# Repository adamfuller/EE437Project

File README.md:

# EE437Project
Autonomous robot car with a smartphone interface

# TODO
- [x] Code for servo
- [x] Add screw holes to board (Adam - 10/16)
- [x] Incorporate Arduino IC into board (Adam - 10/15)
- [x] Add signal lights (forward, backward, turn)
- [x] Design signal lights board
- [ ] Finalize Controller Board Design
- [ ] Submit board design and parts list
- [ ] Assemble board
- [ ] Test board

# Parts List
## Controller Board
- [ ] 1x ATMega328 IC
- [ ] 1x 16 MHz Crystal
- [ ] 1x 28pin socket
- [ ] 1x 4 pin header - male
- [ ] 1x 3 pin header - male
- [ ] 1x 6 pin header - female 90°
- [ ] 2x 2 slot terminal blocks
- [ ] 2x 2x6 header - male
- [ ] 1x power jack
- [ ] 8x 1n4004 diodes
- [ ] 2x 220uF capacitor
- [ ] 2x 20pF capacitor
- [ ] 2x 1k resistor
- [ ] 1x 2k resistor
- [ ] 1x 5mm LED
- [ ] Wire

## Signal Lights Board
- [ ] 12x 5mm LED
- [ ] 4x 300 resistor
- [ ] 4x 4 pin header - male

# Stand-alone Custom Board

# Stand-alone Custom Board Schematic

# Stand-alone Custom Board Manufacturing Preview

## Top

## Bottom

# Custom Shield Board

# Custom Shield Schematic

# Custom Shield Manufacturing Preview

## Top

## Bottom

# Reduced Custom Board

# Reduced Custom Board Schematic

# Reduced Custom Board Manufacturing Preview

## Top

## Bottom

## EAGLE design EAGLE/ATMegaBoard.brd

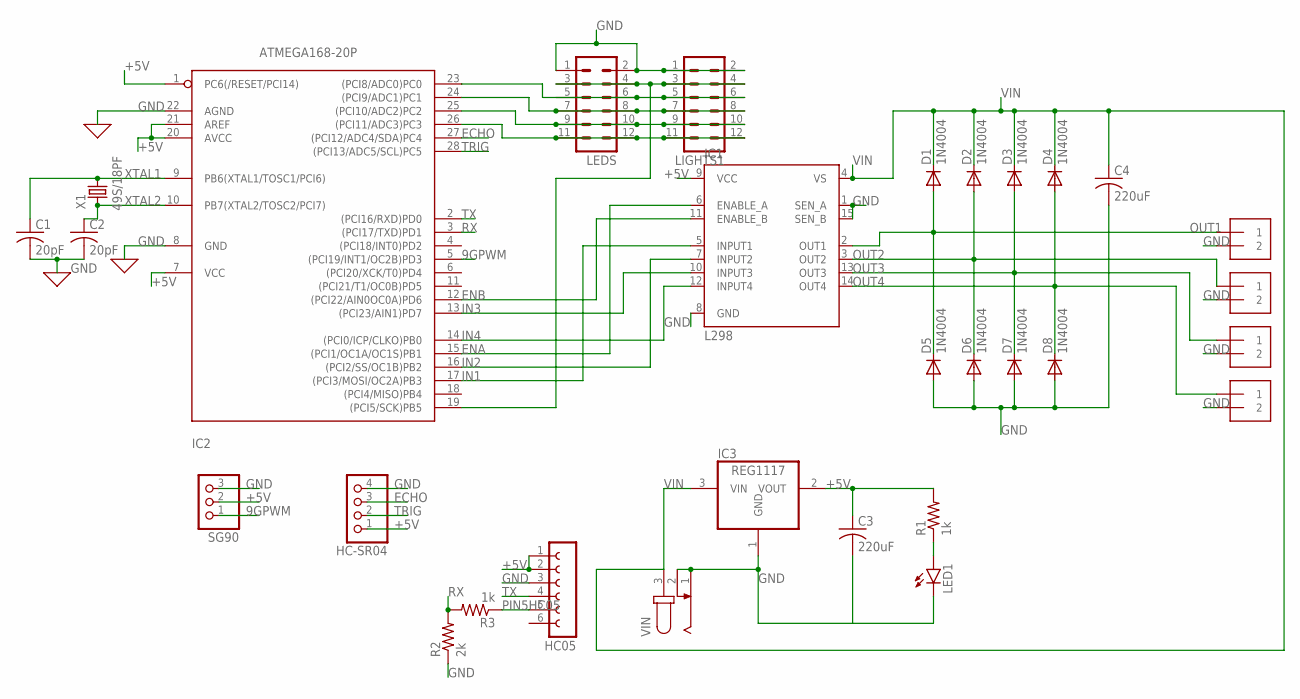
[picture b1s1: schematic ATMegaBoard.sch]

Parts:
C1, C2: 20pF; C050-024X044
C3, C4: 220uF; C050-024X044
D1, D2, D3, D4, D5, D6, D7, D8: 1N4004; DO41-10
HC05: FE06W
HC-SR04: PINHD-1X4; 1X04
IC1: L298; MULTIWATT-15
IC2: ATMEGA168-20P; DIL28-3
IC3: REG1117; SOT223
LED1: LED5MM
LEDS: MA06-2
LIGHTS1: MA06-2
OUT1, OUT2, OUT3, OUT4: 1X2-3.5MM
R1, R3: 1k; 0207/10
R2: 2k; 0207/10
SG90: PINHD-1X3; 1X03
VIN: JACK-PLUG1; SPC4078
X1: 49S/18PF; XTAL_HC49

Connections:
9GPWM: IC2.5 ((PCI19/INT1/OC2B)PD3), SG90.1
+5V: C3.1, HC05.1, HC05.2, HC-SR04.1, IC1.9 (VCC), IC2.1 (PC6(/RESET/PCI14)), IC2.7 (VCC), IC2.20 (AVCC), IC2.21 (AREF), IC3.2 (VOUT), R1.2, SG90.2
ECHO: HC-SR04.3, IC2.27 ((PCI12/ADC4/SDA)PC4)
ENA: IC1.6 (ENABLE_A), IC2.15 ((PCI1/OC1A/OC1S)PB1)
ENB: IC1.11 (ENABLE_B), IC2.12 ((PCI22/AIN0OC0A)PD6)
GND: C1.2, C2.2, C3.2, C4.2, D5.A, D6.A, D7.A, D8.A, HC05.3, HC-SR04.4, IC1.1 (SEN_A), IC1.8 (GND), IC1.15 (SEN_B), IC2.8 (GND), IC2.22 (AGND), IC3.1 (GND), LED1.K (C), LEDS.1, LEDS.2, LIGHTS1.1, LIGHTS1.2, OUT1.2, OUT2.2, OUT3.2, OUT4.2, R2.1, SG90.3, VIN.1, VIN.2
IN1: IC1.5 (INPUT1), IC2.17 ((PCI3/MOSI/OC2A)PB3)
IN2: IC1.7 (INPUT2), IC2.16 ((PCI2/SS/OC1B)PB2)
IN3: IC1.10 (INPUT3), IC2.13 ((PCI23/AIN1)PD7)
IN4: IC1.12 (INPUT4), IC2.14 ((PCI0/ICP/CLKO)PB0)
unnamed: IC2.23 ((PCI8/ADC0)PC0), LEDS.5, LEDS.6, LIGHTS1.5, LIGHTS1.6
unnamed: LED1.A, R1.1
unnamed: IC2.24 ((PCI9/ADC1)PC1), LEDS.7, LEDS.8, LIGHTS1.7, LIGHTS1.8
unnamed: IC2.25 ((PCI10/ADC2)PC2), LEDS.9, LEDS.10, LIGHTS1.9, LIGHTS1.10
unnamed: IC2.19 ((PCI5/SCK)PB5), LEDS.3, LEDS.4, LIGHTS1.3, LIGHTS1.4
unnamed: IC2.26 ((PCI11/ADC3)PC3), LEDS.11, LEDS.12, LIGHTS1.11, LIGHTS1.12
OUT1: D1.A, D5.C, IC1.2 (OUT1), OUT1.1
OUT2: D2.A, D6.C, IC1.3 (OUT2), OUT2.1
OUT3: D3.A, D7.C, IC1.13 (OUT3), OUT3.1
OUT4: D4.A, D8.C, IC1.14 (OUT4), OUT4.1
PIN5HC05: HC05.5, R3.1
RX: IC2.3 ((PCI17/TXD)PD1), R2.2, R3.2
TRIG: HC-SR04.2, IC2.28 ((PCI13/ADC5/SCL)PC5)
TX: HC05.4, IC2.2 ((PCI16/RXD)PD0)
VIN: C4.1, D1.C, D2.C, D3.C, D4.C, IC1.4 (VS), IC3.3 (VIN), VIN.3
XTAL1: C1.1, IC2.9 (PB6(XTAL1/TOSC1/PCI6)), X1.2
XTAL2: C2.1, IC2.10 (PB7(XTAL2/TOSC2/PCI7)), X1.1

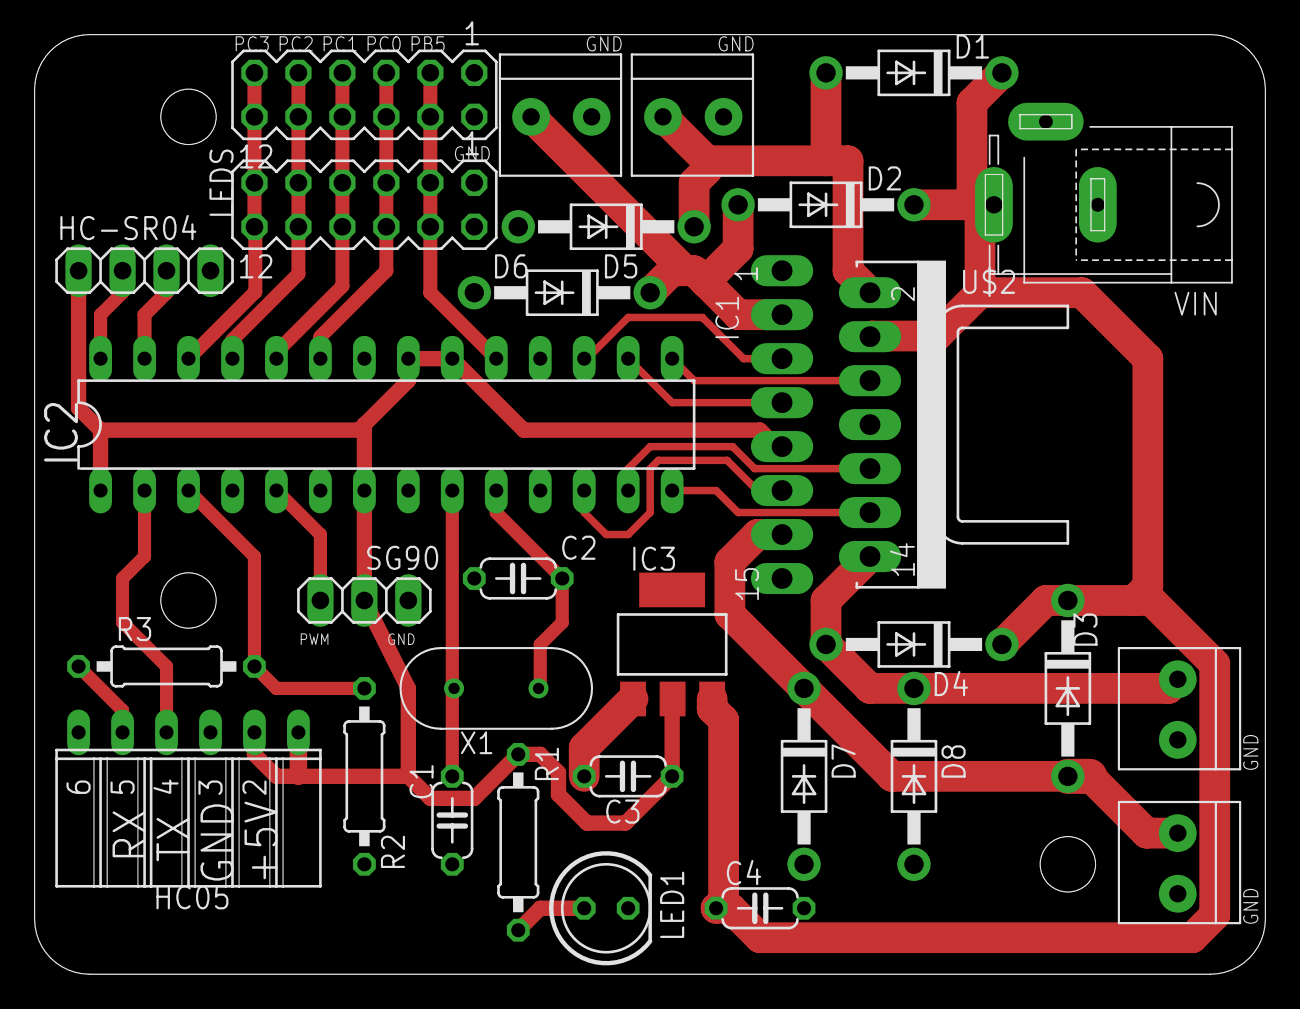
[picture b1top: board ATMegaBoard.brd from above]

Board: 2 copper layers, 71.1 x 54.3 mm, 31 parts (0 on the bottom side), 27 nets.

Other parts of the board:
U$2: D03S

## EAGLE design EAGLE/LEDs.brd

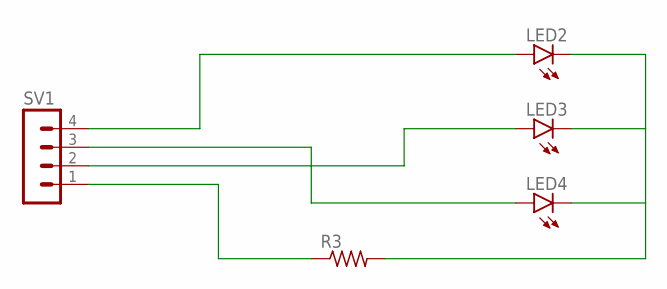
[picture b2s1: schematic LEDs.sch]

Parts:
LED2, LED3, LED4: LED5MM
R3: R-US_0204/7; 0204/7
SV1: MA04-1

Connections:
unnamed: LED2.A, SV1.4
unnamed: LED4.A, SV1.3
unnamed: LED3.A, SV1.2
unnamed: LED2.K (C), LED3.K (C), LED4.K (C), R3.2
unnamed: R3.1, SV1.1

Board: 2 copper layers, 5 parts (0 on the bottom side), 5 nets, no tracks yet.

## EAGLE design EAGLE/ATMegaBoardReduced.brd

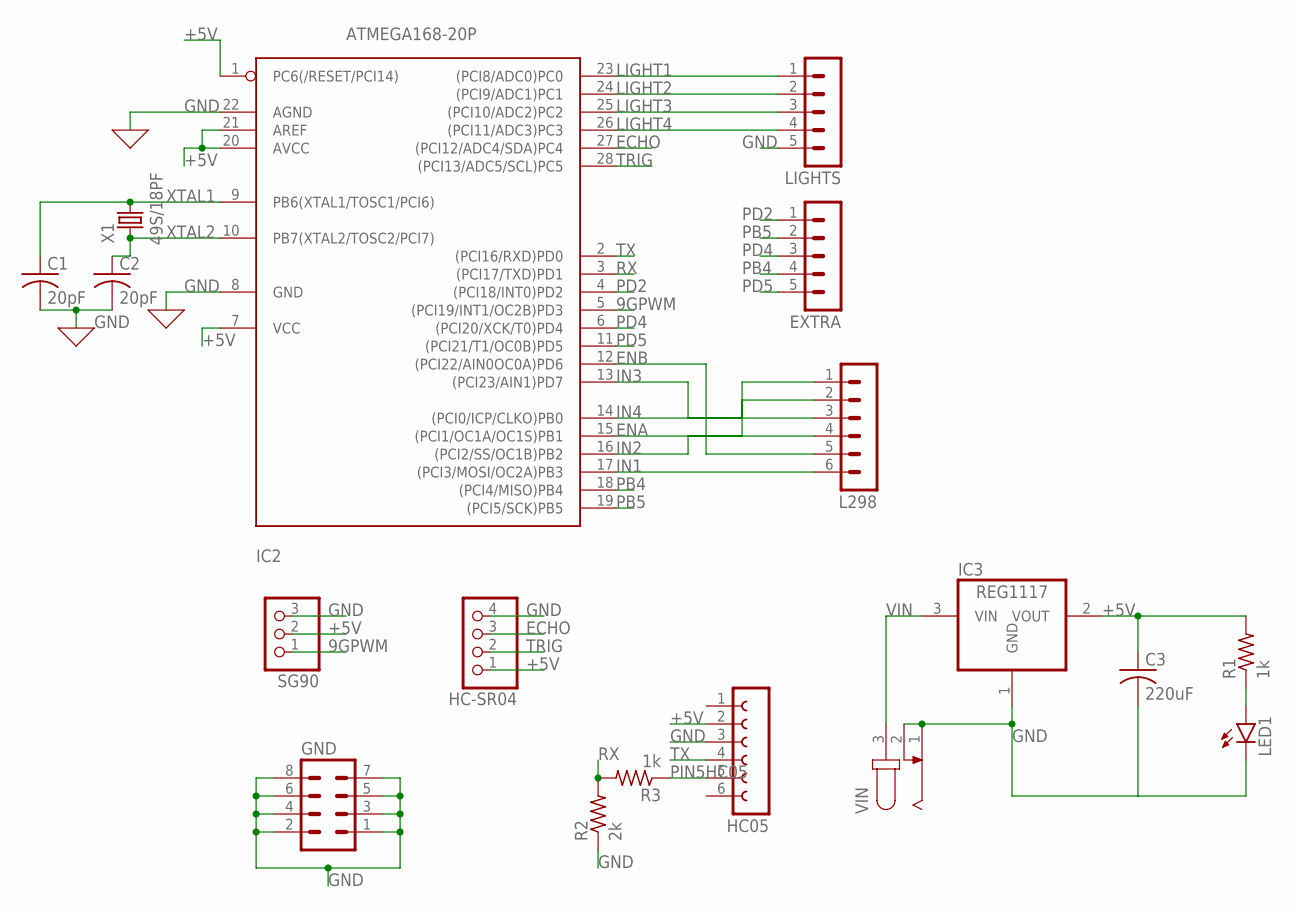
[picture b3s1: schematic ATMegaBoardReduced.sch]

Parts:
C1, C2: 20pF; C050-024X044
C3: 220uF; C050-024X044
EXTRA: MA05-1
GND: MA04-2
HC05: FE06W
HC-SR04: PINHD-1X4; 1X04
IC2: ATMEGA168-20P; DIL28-3
IC3: REG1117; SOT223
L298: MA06-1
LED1: LED5MM
LIGHTS: MA05-1
R1, R3: 1k; 0207/10
R2: 2k; 0207/10
SG90: PINHD-1X3; 1X03
VIN: JACK-PLUG1; SPC4078
X1: 49S/18PF; XTAL_HC49

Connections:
9GPWM: IC2.5 ((PCI19/INT1/OC2B)PD3), SG90.1
+5V: C3.1, HC05.2, HC-SR04.1, IC2.1 (PC6(/RESET/PCI14)), IC2.7 (VCC), IC2.20 (AVCC), IC2.21 (AREF), IC3.2 (VOUT), R1.2, SG90.2
ECHO: HC-SR04.3, IC2.27 ((PCI12/ADC4/SDA)PC4)
ENA: IC2.15 ((PCI1/OC1A/OC1S)PB1), L298.2
ENB: IC2.12 ((PCI22/AIN0OC0A)PD6), L298.5
GND: C1.2, C2.2, C3.2, GND.1, GND.2, GND.3, GND.4, GND.5, GND.6, GND.7, GND.8, HC05.3, HC-SR04.4, IC2.8 (GND), IC2.22 (AGND), IC3.1 (GND), LED1.K (C), LIGHTS.5, R2.1, SG90.3, VIN.1, VIN.2
IN1: IC2.17 ((PCI3/MOSI/OC2A)PB3), L298.6
IN2: IC2.16 ((PCI2/SS/OC1B)PB2), L298.4
IN3: IC2.13 ((PCI23/AIN1)PD7), L298.3
IN4: IC2.14 ((PCI0/ICP/CLKO)PB0), L298.1
LIGHT1: IC2.23 ((PCI8/ADC0)PC0), LIGHTS.1
LIGHT2: IC2.24 ((PCI9/ADC1)PC1), LIGHTS.2
LIGHT3: IC2.25 ((PCI10/ADC2)PC2), LIGHTS.3
LIGHT4: IC2.26 ((PCI11/ADC3)PC3), LIGHTS.4
unnamed: LED1.A, R1.1
PB4: EXTRA.4, IC2.18 ((PCI4/MISO)PB4)
PB5: EXTRA.2, IC2.19 ((PCI5/SCK)PB5)
PD2: EXTRA.1, IC2.4 ((PCI18/INT0)PD2)
PD4: EXTRA.3, IC2.6 ((PCI20/XCK/T0)PD4)
PD5: EXTRA.5, IC2.11 ((PCI21/T1/OC0B)PD5)
PIN5HC05: HC05.5, R3.1
RX: IC2.3 ((PCI17/TXD)PD1), R2.2, R3.2
TRIG: HC-SR04.2, IC2.28 ((PCI13/ADC5/SCL)PC5)
TX: HC05.4, IC2.2 ((PCI16/RXD)PD0)
VIN: IC3.3 (VIN), VIN.3
XTAL1: C1.1, IC2.9 (PB6(XTAL1/TOSC1/PCI6)), X1.2
XTAL2: C2.1, IC2.10 (PB7(XTAL2/TOSC2/PCI7)), X1.1

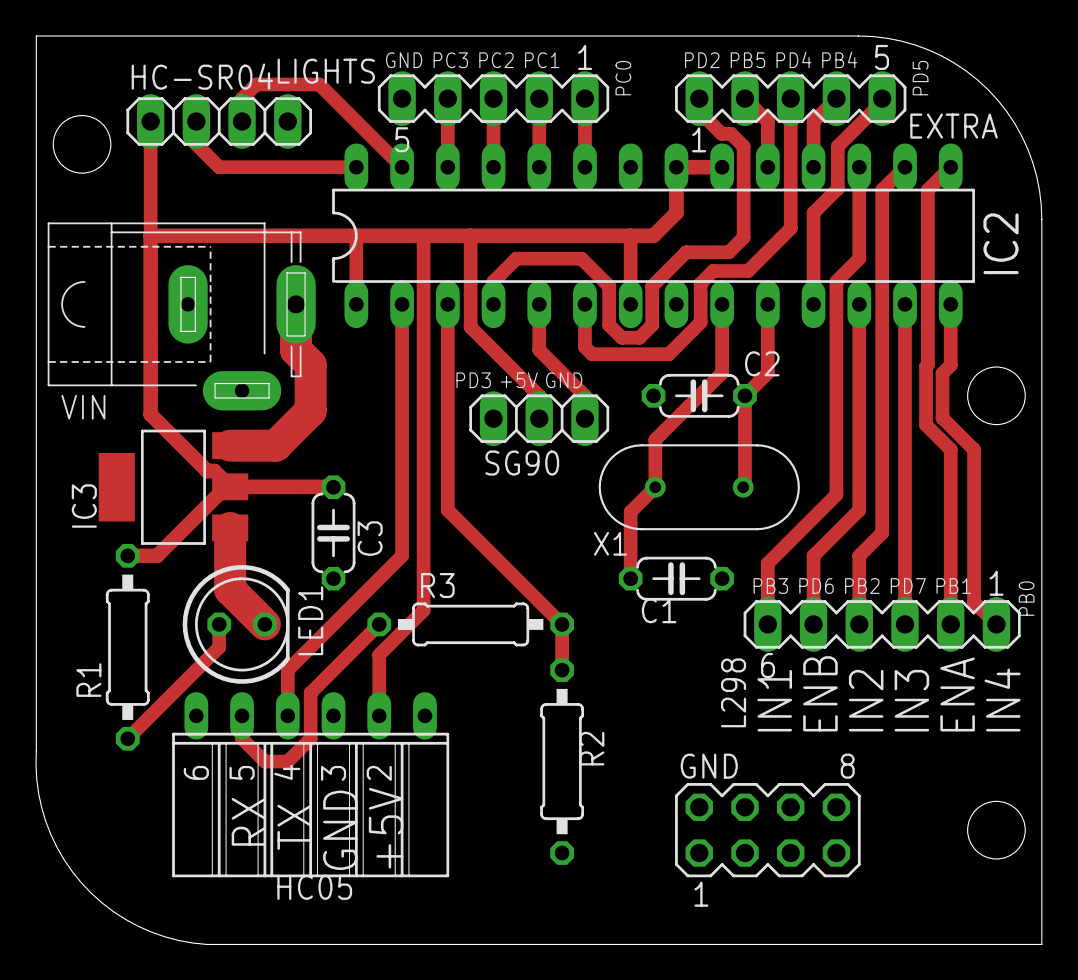
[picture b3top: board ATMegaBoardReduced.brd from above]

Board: 2 copper layers, 55.9 x 50.5 mm, 18 parts (0 on the bottom side), 27 nets.

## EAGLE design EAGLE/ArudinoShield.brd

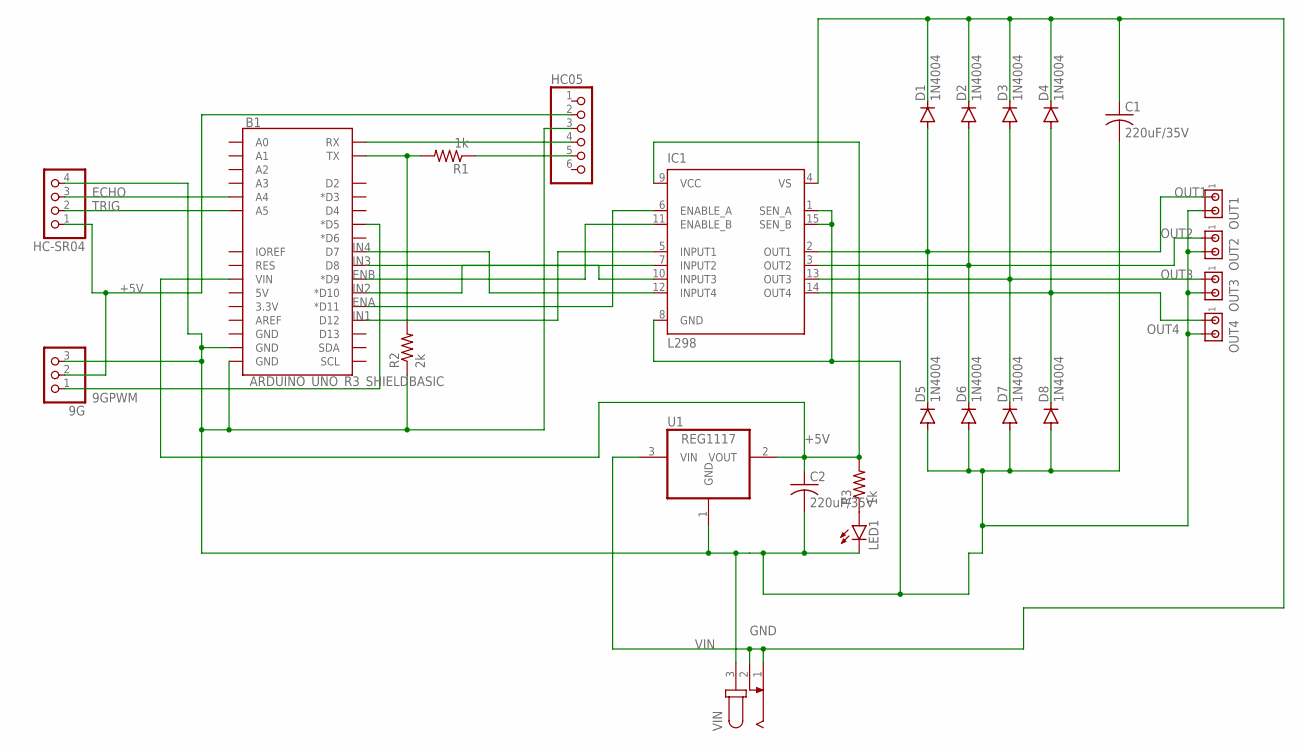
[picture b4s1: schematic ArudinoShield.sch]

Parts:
9G: PINHD-1X3; 1X03
B1: ARDUINO_UNO_R3_SHIELDBASIC; UNO_R3_SHIELD
C1, C2: 220uF/35V; C050-024X044
D1, D2, D3, D4, D5, D6, D7, D8: 1N4004; DO41-10
HC05: PINHD-1X6/90; 1X06/90
HC-SR04: PINHD-1X4; 1X04
IC1: L298; MULTIWATT-15
LED1: LED5MM
OUT1, OUT2, OUT3, OUT4: MTA02-156; 1X2MTA
R1, R3: 1k; 0207/10
R2: 2k; 0207/10
U1: REG1117; SOT223
VIN: JACK-PLUG1; SPC4078

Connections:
9GPWM: 9G.1, B1.D5 (*D5)
+5V: 9G.2, B1.VIN, C2.1, HC05.2, HC-SR04.1, IC1.9 (VCC), R3.2, U1.2 (VOUT)
ECHO: B1.A4, HC-SR04.3
ENA: B1.D11 (*D11), IC1.6 (ENABLE_A)
ENB: B1.D9 (*D9), IC1.11 (ENABLE_B)
GND: 9G.3, B1.GND@0 (GND), B1.GND@1 (GND), C1.2, C2.2, D5.A, D6.A, D7.A, D8.A, HC05.3, HC-SR04.4, IC1.1 (SEN_A), IC1.8 (GND), IC1.15 (SEN_B), LED1.K (C), OUT1.2, OUT2.2, OUT3.2, OUT4.2, R2.1, U1.1 (GND), VIN.3
IN1: B1.D12, IC1.5 (INPUT1)
IN2: B1.D10 (*D10), IC1.7 (INPUT2)
IN3: B1.D8, IC1.10 (INPUT3)
IN4: B1.D7, IC1.12 (INPUT4)
unnamed: B1.TX, R1.2, R2.2
unnamed: B1.RX, HC05.4
unnamed: HC05.5, R1.1
unnamed: LED1.A, R3.1
OUT1: D1.A, D5.C, IC1.2 (OUT1), OUT1.1
OUT2: D2.A, D6.C, IC1.3 (OUT2), OUT2.1
OUT3: D3.A, D7.C, IC1.13 (OUT3), OUT3.1
OUT4: D4.A, D8.C, IC1.14 (OUT4), OUT4.1
TRIG: B1.A5, HC-SR04.2
VIN: C1.1, D1.C, D2.C, D3.C, D4.C, IC1.4 (VS), U1.3 (VIN), VIN.1, VIN.2

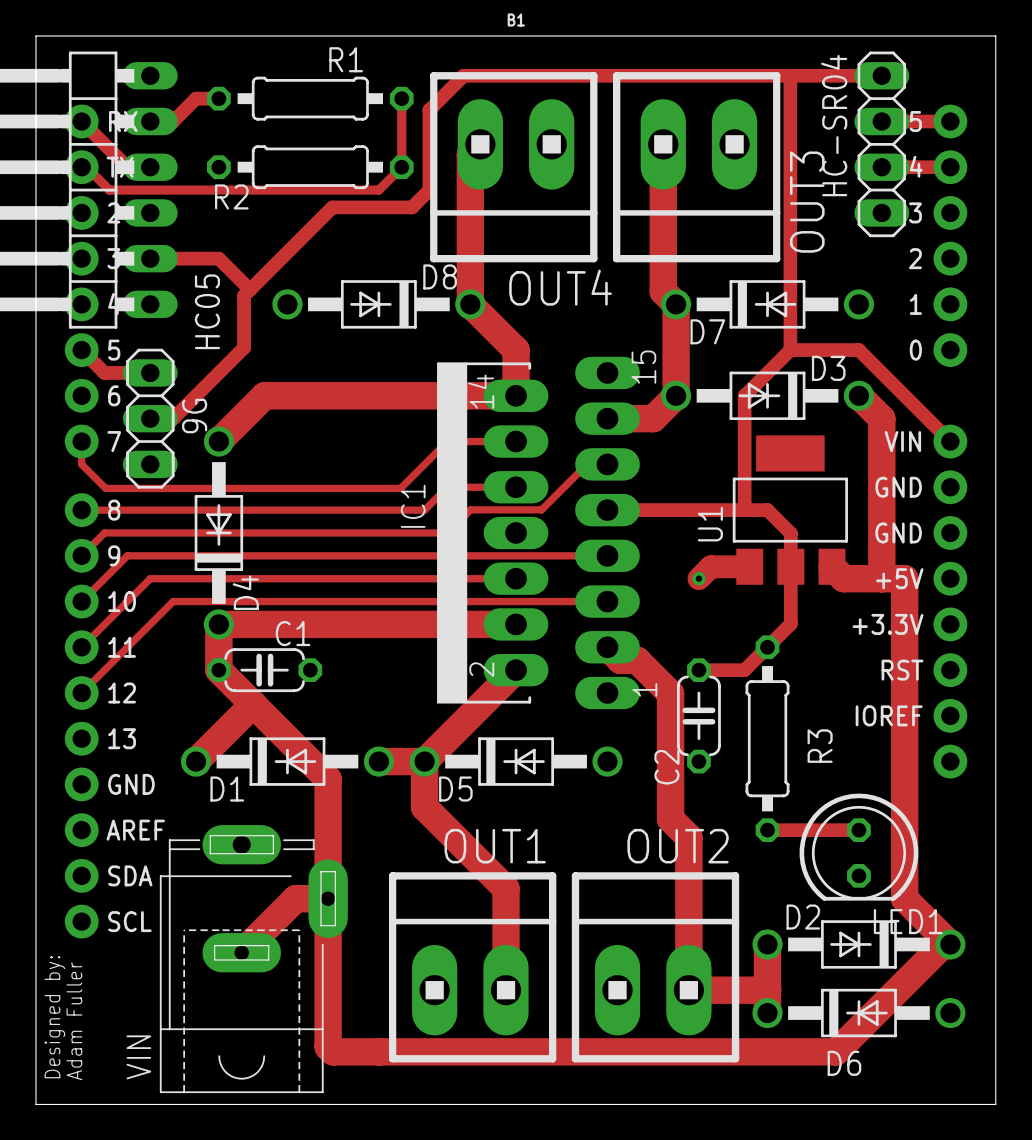
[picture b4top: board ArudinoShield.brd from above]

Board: 2 copper layers, 53.3 x 59.4 mm, 25 parts (0 on the bottom side), 20 nets.

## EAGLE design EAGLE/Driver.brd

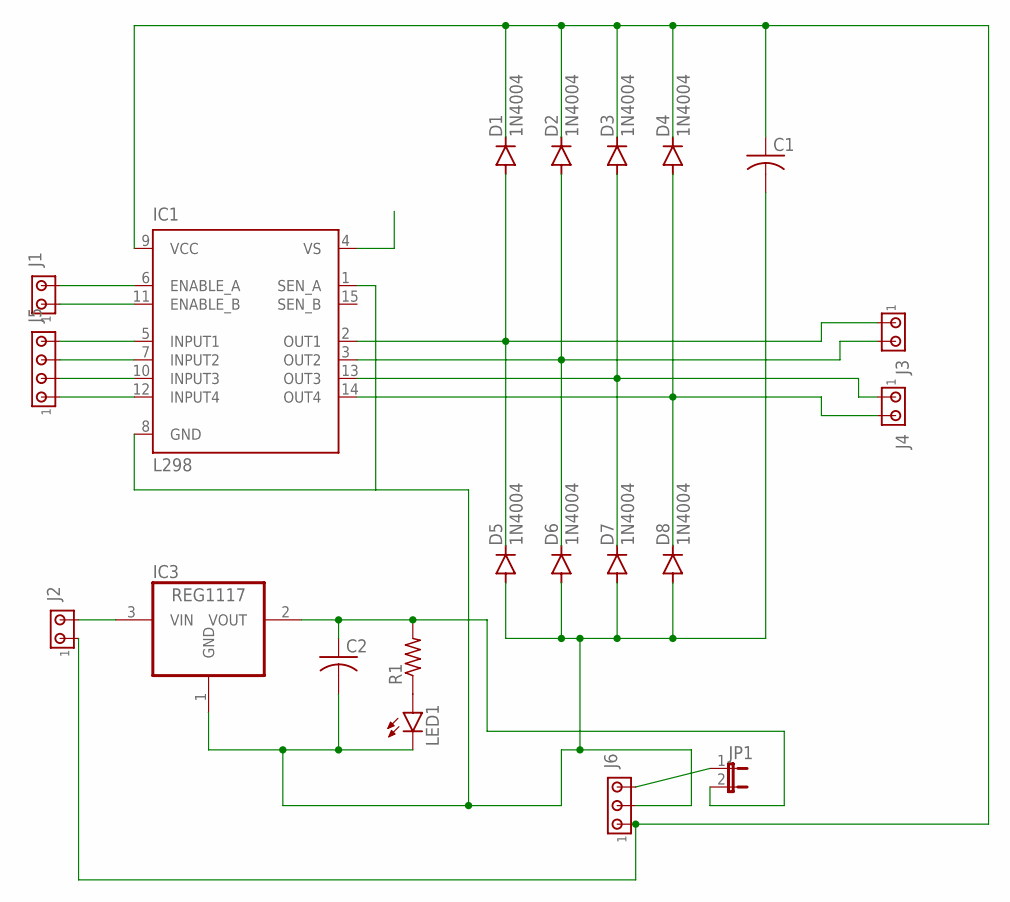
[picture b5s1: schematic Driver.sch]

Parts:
C1, C2: C-US050-024X044; C050-024X044
D1, D2, D3, D4, D5, D6, D7, D8: 1N4004; DO41-10
IC1: L298; MULTIWATT-15
IC3: REG1117; SOT223
J1, J2, J3, J4: MTA02-156; 1X2MTA
J5: MTA04-156; 1X4MTA
J6: MTA03-100; 10X03MTA
JP1: JP1E; JP1
LED1: LED5MM
R1: R-US_0207/10; 0207/10

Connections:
unnamed: D1.A, D5.C, IC1.2 (OUT1), J3.1
unnamed: D2.A, D6.C, IC1.3 (OUT2), J3.2
unnamed: D3.A, D7.C, IC1.13 (OUT3), J4.1
unnamed: D4.A, D8.C, IC1.14 (OUT4), J4.2
unnamed: IC1.6 (ENABLE_A), J1.2
unnamed: IC1.11 (ENABLE_B), J1.1
unnamed: IC1.5 (INPUT1), J5.4
unnamed: IC1.7 (INPUT2), J5.3
unnamed: IC1.10 (INPUT3), J5.2
unnamed: IC1.12 (INPUT4), J5.1
unnamed: C1.2, C2.2, D5.A, D6.A, D7.A, D8.A, IC1.1 (SEN_A), IC1.8 (GND), IC3.1 (GND), J6.2, LED1.K (C)
unnamed: J6.3, JP1.1
unnamed: LED1.A, R1.1
unnamed: C2.1, IC3.2 (VOUT), JP1.2, R1.2
unnamed: IC3.3 (VIN), J2.2
unnamed: C1.1, D1.C, D2.C, D3.C, D4.C, IC1.9 (VCC), J2.1, J6.1

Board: 2 copper layers, 21 parts (0 on the bottom side), 16 nets, no tracks yet.

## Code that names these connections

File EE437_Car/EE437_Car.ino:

#include <Servo.h>


#define ECHO_PIN  A4 // PC4
#define TRIG_PIN  A5 // PC5
#define ENA_PIN   5
#define ENB_PIN   11
#define IN1_PIN   6 // Right forward
#define IN2_PIN   7 // Right backward
#define IN3_PIN   8 // Left backward
#define IN4_PIN   9 // Left forward
#define SERVO_PIN     3 

uint8_t btOutput;
int intent, extent;
uint8_t cache[8] = {0x00, 0x00, 0x00, 0x00, 0x00, 0x00, 0x00, 0x00};
bool checkedLastTime = false;
bool shouldBrake;
Servo servo;

int getDistance() {
  digitalWrite(TRIG_PIN, LOW);
  delayMicroseconds(2);
  digitalWrite(TRIG_PIN, HIGH);
  delayMicroseconds(10);
  digitalWrite(TRIG_PIN, LOW);
  return (int)pulseIn(ECHO_PIN, HIGH, 1583) / 58;
}

void brake(){
  analogWrite(ENA_PIN, 0);
  analogWrite(ENB_PIN, 0);
  analogWrite(IN1_PIN, 0);
//  PORTD&=0x3F; // Set IN2 and IN3 low
  analogWrite(IN2_PIN, 0);
  analogWrite(IN3_PIN, 0);
  analogWrite(IN4_PIN, 0);
}

void spinRight(){
  analogWrite(ENA_PIN, 255);
  analogWrite(ENB_PIN, 255);
  analogWrite(IN1_PIN, 0);
  analogWrite(IN2_PIN, 255);
  analogWrite(IN3_PIN, 0);
  analogWrite(IN4_PIN, 255);
}

void spinLeft(){
  analogWrite(ENA_PIN, 255);
  analogWrite(ENB_PIN, 255);
  analogWrite(IN1_PIN, 255);
  analogWrite(IN2_PIN, 0);
  analogWrite(IN3_PIN, 255);
  analogWrite(IN4_PIN, 0);
}

int steeringAngle(){
  int leftPower = (int)((((cache[0x06]) & 0x1F) / 31.0) * 255 );
  int rightPower = (int)((((cache[0x05]) & 0x1F) / 31.0) * 255 );
  if (leftPower == rightPower) return 90;
  return (int)((rightPower * 1.0 / (rightPower + leftPower) * 1.0) * 178) + 1;
}

void performTask(int task){
  switch (task){
    case 0x00:
      brake();
      break;
    case 0x01:
      spinRight();
      break;
    case 0x02:
      spinLeft();
      break;
    default:
      break;
  }
}

void setup() {
  Serial.begin(9600);
  pinMode(ECHO_PIN, INPUT);
  pinMode(TRIG_PIN, OUTPUT);
  pinMode(IN1_PIN, OUTPUT);
  pinMode(IN2_PIN, OUTPUT);
  pinMode(IN3_PIN, OUTPUT);
  pinMode(IN4_PIN, OUTPUT);
  pinMode(ENA_PIN, OUTPUT);
  pinMode(ENB_PIN, OUTPUT);
  servo.attach(SERVO_PIN);

  pinMode(LED_BUILTIN, OUTPUT);
}

void loop() {
  // Only check to brake every other time
  if (!checkedLastTime){
    int dist = getDistance();  
    // Check if we should brake.
    shouldBrake = abs(dist) <= 20 && abs(dist) != 0;
  }
  
  checkedLastTime = !checkedLastTime;

  // Check for next command(s)
  for (int i = 0; i< 10; i++){
    if (Serial.available()){
      btOutput = Serial.read();
      cache[(btOutput & 0xE0) >> 5] = btOutput;
    } else {
      break;
    }
  }

  if (shouldBrake){

    // Ensure we shouldn't be braking or going in reverse
    if ( cache[0x07] != 0xE0 && (cache[0x02]&0x1F != 0x00 || cache[0x03]&0x1F != 0x00) ){
      analogWrite(IN2_PIN, (int)((((cache[0x02]) & 0x1F) / 31.0) * 255 ));
      analogWrite(IN3_PIN, (int)((((cache[0x03]) & 0x1F) / 31.0) * 255 ));
      analogWrite(ENA_PIN, (int)((((cache[0x05]) & 0x1F) / 31.0) * 255 ));
      analogWrite(ENB_PIN, (int)((((cache[0x06]) & 0x1F) / 31.0) * 255 ));
    } else {
      brake();
    }
    return;
  }

  servo.write(steeringAngle());

  for (intent = 0x01; intent < 0x08; intent++){
    extent = (int)((((cache[intent]) & 0x1F) / 31.0) * 255 );

    // Continue if this command is used (bits 5-7 cleared)
    if ((cache[intent] & 0xE0) == 0x00) continue;
    
    // return the command to the controller ( this is used to reduce sending repeat commands )
    Serial.print(cache[intent]);
    
    switch (intent){
      case 0x01:
        // IN1
        analogWrite(IN1_PIN, extent);
        break;
      case 0x02:
        // IN2
        analogWrite(IN2_PIN, extent);
        break;
      case 0x03:
        // IN3
        analogWrite(IN3_PIN, extent);
        break;
      case 0x04:
        // IN4
        analogWrite(IN4_PIN, extent);
        break;
      case 0x05:
        // ENA
        analogWrite(ENA_PIN, extent);
        break;
      case 0x06:
        // ENB
        analogWrite(ENB_PIN, extent);
        break;
       case 0x07:
        // Multi-command tasks
        performTask(cache[intent] & 0x1F);
        break;
      default:
        break;
    }
    // Set the command as used (clear bits 5-7)
    cache[intent] = cache[intent] & 0x1F;
  }
}

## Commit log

2019-09-22 Moved conversion inside methods, added ENA and ENB controls
2019-09-22 Added PAIR method to possible controls
2019-09-22 Replaced boolean conversion with string comparison
2019-09-22 Replaced exact string compare with contains
2019-09-22 Switched to gyroscope controls, updated UI, added center, neutral, and show data button
2019-09-22 added gitignore
2019-09-23 Added icon, SteeringService, sends over bluetooth, many bug fixes and improvements
2019-09-23 Improved steering and reduced data sent to changes in state
2019-09-23 Added initial driver schematics
2019-09-23 Converted BluetoothService to singleton-like class
2019-09-23 Removed unused outputs on functions
2019-09-23 Removed TODO
2019-09-23 Removed unused normalizedListener
2019-09-23 major refactoring
2019-09-23 fixed internal imports
2019-09-23 first iOS run, always show controls toggle
2019-09-24 refactor
2019-09-24 added initial automated stopping script
2019-09-24 removed prints from main
2019-09-24 Changed ∆ to d
2019-09-24 setup pins
2019-09-24 fixing runtime errors
2019-09-24 added channel input to callbacks
2019-09-24 switched to use echo rising and falling edge
2019-09-24 added print statement
2019-09-24 use both rising and falling edge
2019-09-24 reset has_been_triggered flag
2019-09-26 added arduino code, minor app changes
2019-09-26 Switched to single byte control method
2019-09-26 Allow for full gyro controls
2019-09-26 Added forward collision avoidance
2019-09-27 Restructured command building process
2019-09-29 fixed bug where max throttle came out as no throttle
2019-09-29 removed python code for controls
2019-09-29 Added tasks to arduino code, updated signal refresh speed
2019-09-30 Added Arduino Shield schematic
2019-09-30 renamed component, updated ignore
2019-09-30 added routes to board
2019-09-30 reduced schematic
2019-09-30 Reduced shield schematic
2019-10-01 added proposal and images
2019-10-01 added board image
2019-10-02 upgraded schematic picture
2019-10-02 fixed typo
2019-10-02 higher res board picture
2019-10-02 added values, updated gitignore for eagle files
2019-10-02 added L298 data sheet
2019-10-02 updated schematic for proper pinout from L298 and added supply voltage terminal block
2019-10-02 updated board and schematic images
2019-10-02 updated schematic and board
2019-10-02 updated power trace size
2019-10-02 added ground plane, updated layout
2019-10-02 updated board and previews
2019-10-03 fixed L298 pin 8 not being reliably grounded
2019-10-03 By hand rework of board layout, no vias
2019-10-03 increased minimum trace width
2019-10-03 minor changes, updated images
2019-10-03 minor board changes
2019-10-03 reworked to fit on top of arduino
2019-10-03 updated images
2019-10-03 cropped previews
2019-10-03 Update README.md
    fixed only showing top preview, changed to dynamic scaling
2019-10-03 minor changes
2019-10-03 updated schematic and board to use DC jack
2019-10-04 shifted L298 to make room for heat sink
2019-10-04 moved all images
2019-10-04 added onDisconnect callback, refactoring and documentation
2019-10-09 added new arduino code for custom board
2019-10-09 moved all EAGLE files into own folder
2019-10-14 updated to power peripherals from regulator, updated line width
2019-10-14 moved Vin inside board
2019-10-14 added docs
2019-10-14 added breadboard layout
2019-10-15 Began New Arduino Board
2019-10-16 added standalone board
2019-10-17 updated ATMegaBoard, added CAM files
2019-10-17 Switched to female header for HC05
2019-10-17 compressed board
2019-10-18 Fixed bug where unable to reconnect when disconnected from board
2019-10-18 added servo support, reduced to single cache with intent as indexing
2019-10-18 updated to reduce unnecessary repeated commands
2019-10-18 switch cache to bytes not ints, added reverse on sensor braking
2019-10-18 First version of reduced board
2019-10-18 updated layout
2019-10-18 oops
2019-10-18 removed unnecessary image
2019-10-18 fixed spelling
2019-10-18 minor layout changes
2019-10-21 set reset pin high added ground pins
2019-10-21 shifted HC-SR04 away from ATMega
2019-10-22 minor board updates
2019-10-22 updated board to change mounted orientation
2019-10-22 updated for final board decision, added parts list
2019-10-22 -Isaiah added LED boards
2019-10-22 updated output for LEDs
2019-10-22 expanded LED lighting to be 1 to 1
2019-10-23 reduced update frequency from 15ms to 50ms
2019-10-23 updated on only check distance every other loop
2019-10-23 increased clearance between LEDs and D6
2019-10-28 set EN on HC-05 to +5v
2019-10-29 added higher speed code
2019-10-29 removed DPM of PORTD from brake
2019-10-29 updated transmission frequency from 50mS to 16 mS
2019-10-30 reworked distance measurement methodology
2019-10-30 updated for using custom PWM
2019-11-01 implemented UART interrupt, enabled GPIO using asm macro, reduced main loop if statements
2019-11-04 added ATmega328 datasheet
2019-11-04 Working update
2019-11-07 "less optimal" but actually works
2019-12-04 fixed no braking bug

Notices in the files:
parts and their libraries:
SparkFun-Boards: Licensing: Creative Commons ShareAlike 4.0 International - https://creativecommons.org/licenses/by-sa/4.0
